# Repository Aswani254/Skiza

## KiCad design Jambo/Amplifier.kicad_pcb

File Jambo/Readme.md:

# Audio amp circuit from the book "High Power Audio Amplifier Construction Manual"
# THD is claimed to be 
# Maximum power is 120 Watts RMS into an 8 ohm load

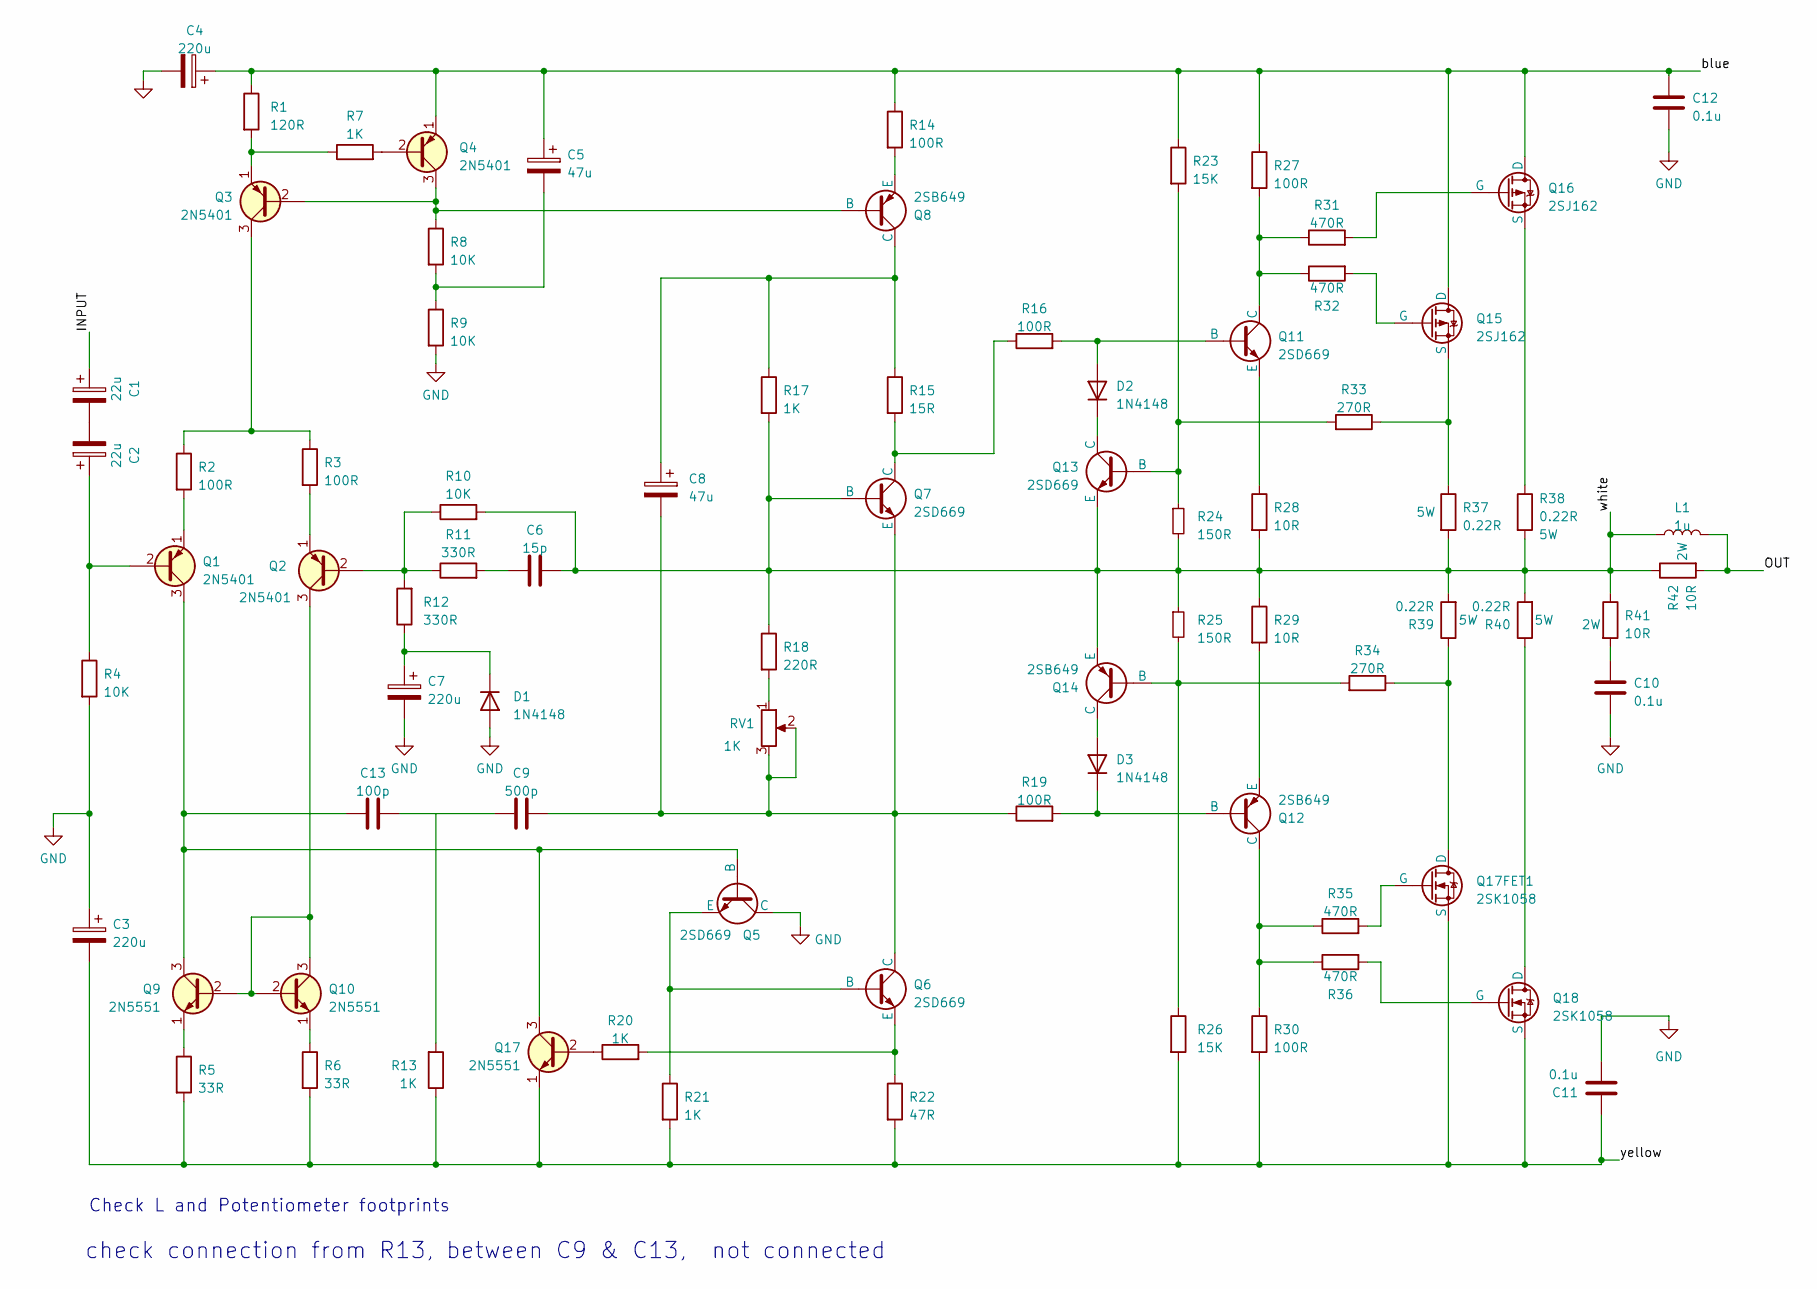
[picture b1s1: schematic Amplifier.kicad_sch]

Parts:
C1, C2: 22u; CP_Radial_D7.5mm_P2.50mm
C3, C4, C7: 220u; CP_Radial_D7.5mm_P2.50mm
C5, C8: 47u; CP_Radial_D7.5mm_P2.50mm
C6: 15p; C_Disc_D5.0mm_W2.5mm_P2.50mm
C9: 500p; C_Disc_D5.0mm_W2.5mm_P2.50mm
C10, C11, C12: 0.1u; C_Disc_D5.0mm_W2.5mm_P2.50mm
C13: 100p; C_Disc_D5.0mm_W2.5mm_P2.50mm
D1, D2, D3: 1N4148; D_DO-35_SOD27_P7.62mm_Horizontal
L1: 1u; L_Radial_D13.5mm_P7.00mm_Fastron_09HCP
Q1, Q2, Q3, Q4: 2N5401; TO-92_Wide
Q5, Q6, Q7, Q11, Q13: 2SD669; TO-126-3_Vertical
Q8, Q12, Q14: 2SB649; TO-126-3_Vertical
Q9, Q10, Q17: 2N5551; TO-92_Wide
Q15, Q16: 2SJ162; TO-3P-3_Vertical
Q17FET1, Q18: 2SK1058; TO-3P-3_Vertical
R1: 120R; R_Axial_DIN0207_L6.3mm_D2.5mm_P7.62mm_Horizontal
R2, R3, R14, R16, R19, R27, R30: 100R; R_Axial_DIN0207_L6.3mm_D2.5mm_P7.62mm_Horizontal
R4, R8, R9, R10: 10K; R_Axial_DIN0207_L6.3mm_D2.5mm_P7.62mm_Horizontal
R5, R6: 33R; R_Axial_DIN0207_L6.3mm_D2.5mm_P7.62mm_Horizontal
R7, R13, R17, R20, R21: 1K; R_Axial_DIN0207_L6.3mm_D2.5mm_P7.62mm_Horizontal
R11, R12: 330R; R_Axial_DIN0207_L6.3mm_D2.5mm_P7.62mm_Horizontal
R15: 15R; R_Axial_DIN0207_L6.3mm_D2.5mm_P7.62mm_Horizontal
R18: 220R; R_Axial_DIN0207_L6.3mm_D2.5mm_P7.62mm_Horizontal
R22: 47R; R_Axial_DIN0207_L6.3mm_D2.5mm_P7.62mm_Horizontal
R23, R26: 15K; R_Axial_DIN0207_L6.3mm_D2.5mm_P7.62mm_Horizontal
R24, R25: 150R; R_Axial_DIN0207_L6.3mm_D2.5mm_P7.62mm_Horizontal
R28, R29: 10R; R_Axial_DIN0207_L6.3mm_D2.5mm_P7.62mm_Horizontal
R31, R32, R35, R36: 470R; R_Axial_DIN0207_L6.3mm_D2.5mm_P7.62mm_Horizontal
R33, R34: 270R; R_Axial_DIN0207_L6.3mm_D2.5mm_P7.62mm_Horizontal
R37, R38, R39, R40: 0.22R; R_Axial_DIN0617_L17.0mm_D6.0mm_P7.62mm_Vertical
R41, R42: 10R; R_Axial_DIN0414_L11.9mm_D4.5mm_P5.08mm_Vertical
RV1: 1K; Potentiometer_Bourns_3266Y_Vertical

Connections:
/INPUT: C1.1
/OUT: L1.2, R42.2
/blue: C4.1, C5.1, C12.2, Q4.1 (E), Q15.1 (D), Q16.1 (D), R1.1, R14.1, R23.1, R27.1
/white: C6.2, L1.1, Q7.2 (B), Q13.3 (E), Q14.3 (E), R10.2, R17.2, R18.1, R24.2, R25.1, R28.2, R29.1, R37.2, R38.2, R39.2, R40.2, R41.1, R42.1
/yellow: C3.2, C11.2, Q17.1 (E), Q17FET1.3 (S), Q18.3 (S), R5.2, R6.2, R13.1, R21.2, R22.2, R26.2, R30.2
GND: C3.1, C4.2, C7.2, C10.1, C11.1, C12.1, D1.2 (A), Q5.1 (C), R4.2, R9.2
unnamed: C1.2, C2.2
unnamed: C5.2, R8.2, R9.1
unnamed: C6.1, R11.2
unnamed: C10.2, R41.2
unnamed: C9.1, C13.2
unnamed: C7.1, D1.1 (K), R12.1
unnamed: D2.2 (A), Q11.2 (B), R16.2
unnamed: D2.1 (K), Q13.1 (C)
unnamed: D3.2 (A), Q14.1 (C)
unnamed: D3.1 (K), Q12.2 (B), R19.2
unnamed: C2.1, Q1.2 (B), R4.1
unnamed: C13.1, Q1.3 (C), Q5.2 (B), Q9.3 (C), Q17.3 (C)
unnamed: Q1.1 (E), R2.2
unnamed: Q2.2 (B), R10.1, R11.1, R12.2
unnamed: Q2.1 (E), R3.2
unnamed: Q3.2 (B), Q4.3 (C), Q8.2 (B), R8.1
unnamed: Q3.3 (C), R2.1, R3.1
unnamed: Q3.1 (E), R1.2, R7.1
unnamed: Q4.2 (B), R7.2
unnamed: Q5.3 (E), Q6.2 (B), R21.1
unnamed: C8.2, C9.2, Q6.1 (C), Q7.3 (E), R19.1, RV1.2, RV1.3
unnamed: Q6.3 (E), R20.2, R22.1
unnamed: Q7.1 (C), R15.2, R16.1
unnamed: C8.1, Q8.1 (C), R15.1, R17.1
unnamed: Q8.3 (E), R14.2
unnamed: Q9.1 (E), R5.1
unnamed: Q2.3 (C), Q9.2 (B), Q10.2 (B), Q10.3 (C)
unnamed: Q10.1 (E), R6.1
unnamed: Q11.1 (C), R27.2, R31.1, R32.1
unnamed: Q11.3 (E), R28.1
unnamed: Q12.1 (C), R30.1, R35.1, R36.1
unnamed: Q12.3 (E), R29.2
unnamed: Q13.2 (B), R23.2, R24.1, R33.2
unnamed: Q14.2 (B), R25.2, R26.1, R34.2
unnamed: Q15.2 (G), R32.2
unnamed: Q15.3 (S), R33.1, R37.1
unnamed: Q16.2 (G), R31.2
unnamed: Q16.3 (S), R38.1
unnamed: Q17.2 (B), R20.1
unnamed: Q17FET1.1 (D), R34.1, R39.1
unnamed: Q17FET1.2 (G), R35.2
unnamed: Q18.1 (D), R40.1
unnamed: Q18.2 (G), R36.2
unnamed: R18.2, RV1.1

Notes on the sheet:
Check L and Potentiometer footprints
check connection from R13, between C9 & C13, not connected

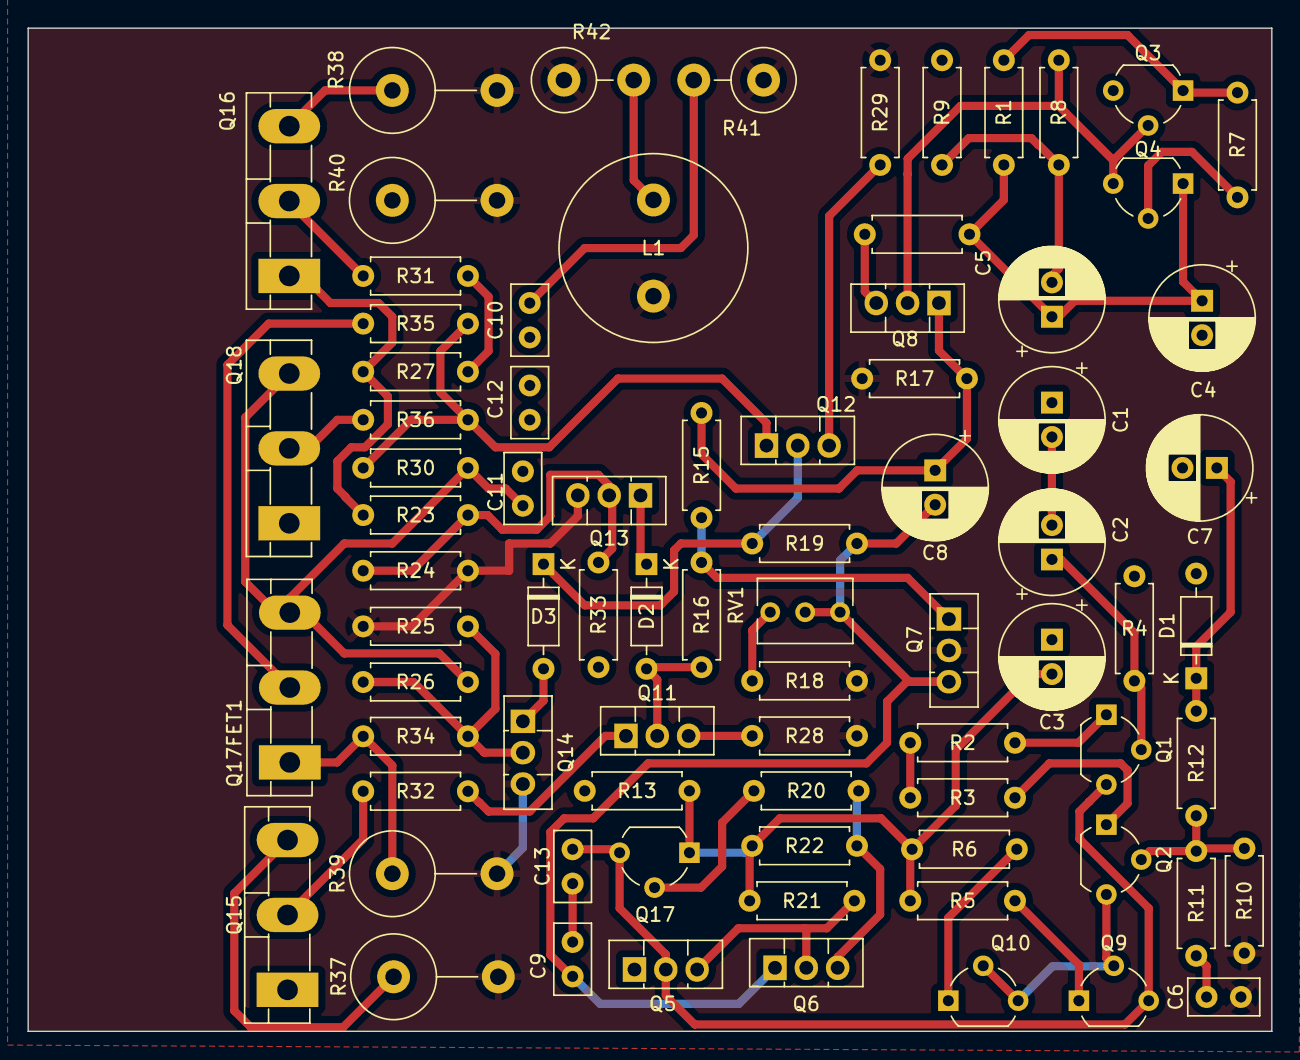
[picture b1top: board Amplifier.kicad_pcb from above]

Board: 2 copper layers, 90.5 x 73.0 mm, 79 parts (0 on the bottom side), 49 nets.

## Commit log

2024-05-26 init: initial commit of Skiza/Jambo Amplifier design files
2024-05-26 docs: update Readme.md
2024-06-18 docs: update Readme
